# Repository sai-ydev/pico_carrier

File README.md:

# pico_carrier
Pico carrier board for the Blues Notecard

## TO DO ##
1. ~~Fix Eagle Lbr~~
2. ~~Fix PCB~~
3. Design StemmaQT Form factor

In the picture below, Raspberry Pi Pico interfaced to the [Blues Notecard](https://blues.io/)

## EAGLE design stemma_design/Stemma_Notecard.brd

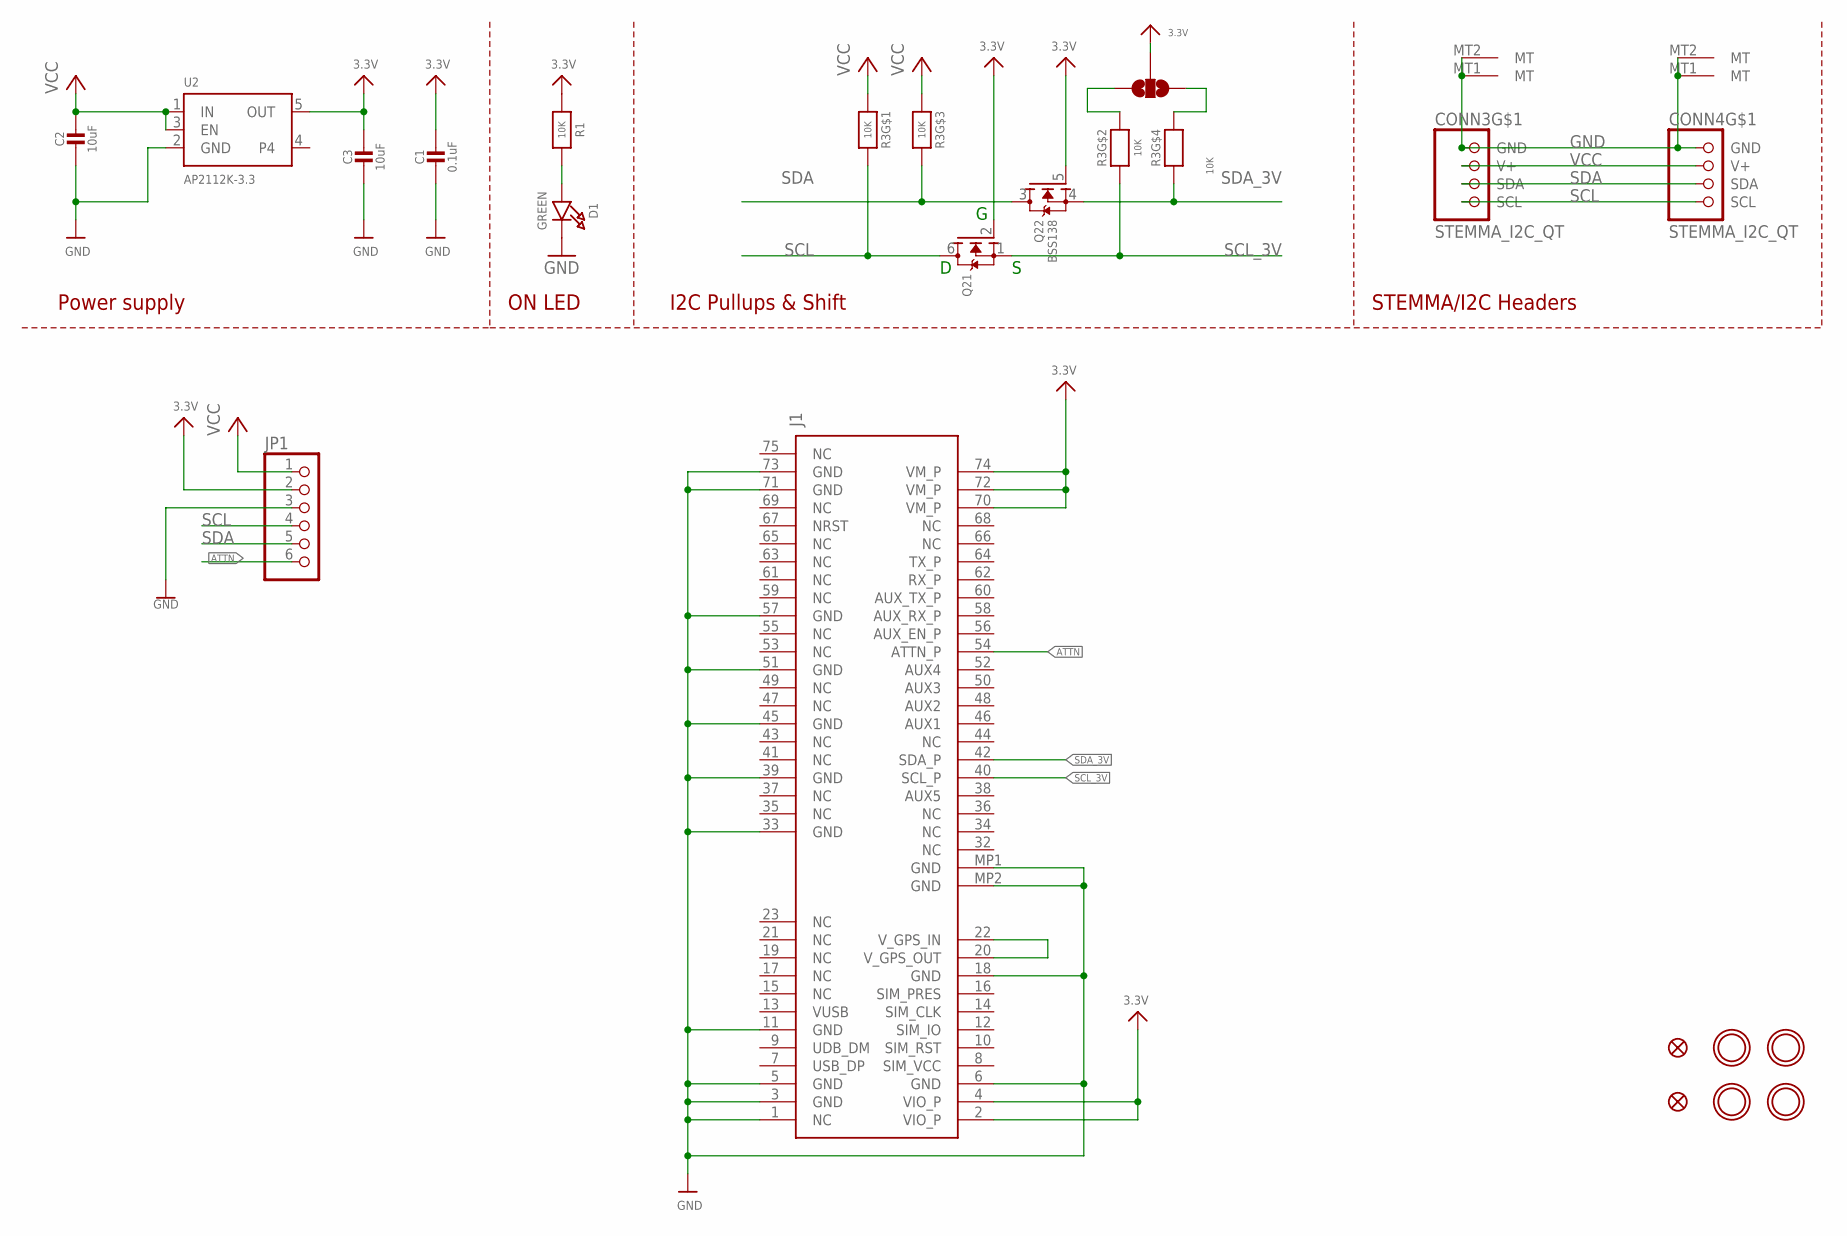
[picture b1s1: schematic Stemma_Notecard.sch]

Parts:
C1: 0.1uF; 0603-NO
C2, C3: 10uF; 0805-NO
CONN3, CONN4: STEMMA_I2C_QT; JST_SH4
D1: GREEN; CHIPLED_0603_NOOUTLINE
FID3, FID4: FIDUCIAL_1MM
J1: MDT420E01001NOTECARD; NOTECARD
JP1: HEADER-1X670MIL; 1X06_ROUND_70
JP2: JUMPER-SMT_3_NO_NO-SILK; SMT-JUMPER_3_NO_NO-SILK
Q2: BSS138; SOT363
R1: 10K; 0603-NO
R3: 10K; RESPACK_4X0603
U2: AP2112K-3.3; SOT23-5
U$1, U$17, U$19, U$21: MOUNTINGHOLE2.5; MOUNTINGHOLE_2.5_PLATED

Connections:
3.3V: C1.1, C3.1, J1.2 (VIO_P), J1.4 (VIO_P), J1.70 (VM_P), J1.72 (VM_P), J1.74 (VM_P), JP1.2, JP2.2, Q2.2 (G), Q2.5 (G), R1.1, U2.5 (OUT)
ATTN: J1.54 (ATTN_P), JP1.6
GND: C1.2, C2.2, C3.2, CONN3.1 (GND), CONN3.MT1 (MT), CONN3.MT2 (MT), CONN4.1 (GND), CONN4.MT1 (MT), CONN4.MT2 (MT), D1.C, J1.1 (NC), J1.3 (GND), J1.5 (GND), J1.6 (GND), J1.11 (GND), J1.18 (GND), J1.33 (GND), J1.39 (GND), J1.45 (GND), J1.51 (GND), J1.57 (GND), J1.71 (GND), J1.73 (GND), J1.MP1 (GND), J1.MP2 (GND), JP1.3, U2.2 (GND)
unnamed: D1.A, R1.2
unnamed: J1.20 (V_GPS_OUT), J1.22 (V_GPS_IN)
unnamed: JP2.3, R3.2 (1)
unnamed: JP2.1, R3.4 (1)
SCL: CONN3.4 (SCL), CONN4.4 (SCL), JP1.4, Q2.6 (D), R3.8 (2)
SCL_3V: J1.40 (SCL_P), Q2.1 (S), R3.7 (2)
SDA: CONN3.3 (SDA), CONN4.3 (SDA), JP1.5, Q2.3 (D), R3.6 (2)
SDA_3V: J1.42 (SDA_P), Q2.4 (S), R3.5 (2)
VCC: C2.1, CONN3.2 (V+), CONN4.2 (V+), JP1.1, R3.1, R3.3 (1), U2.1 (IN), U2.3 (EN)

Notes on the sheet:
I2C Pullups & Shift
STEMMA/I2C Headers
ON LED
Power supply

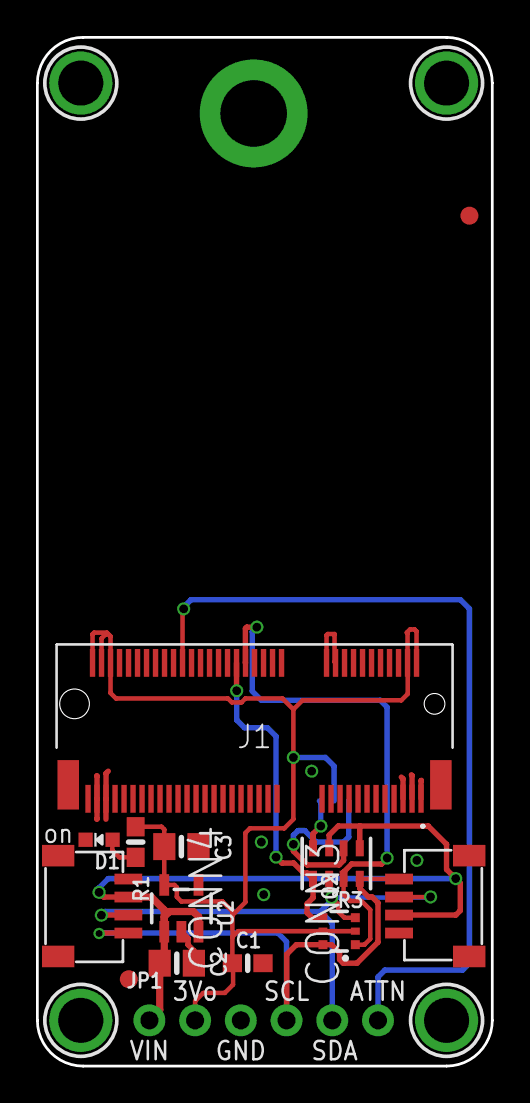
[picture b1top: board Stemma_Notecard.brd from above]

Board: 2 copper layers, 25.3 x 57.1 mm, 19 parts (1 on the bottom side), 12 nets.

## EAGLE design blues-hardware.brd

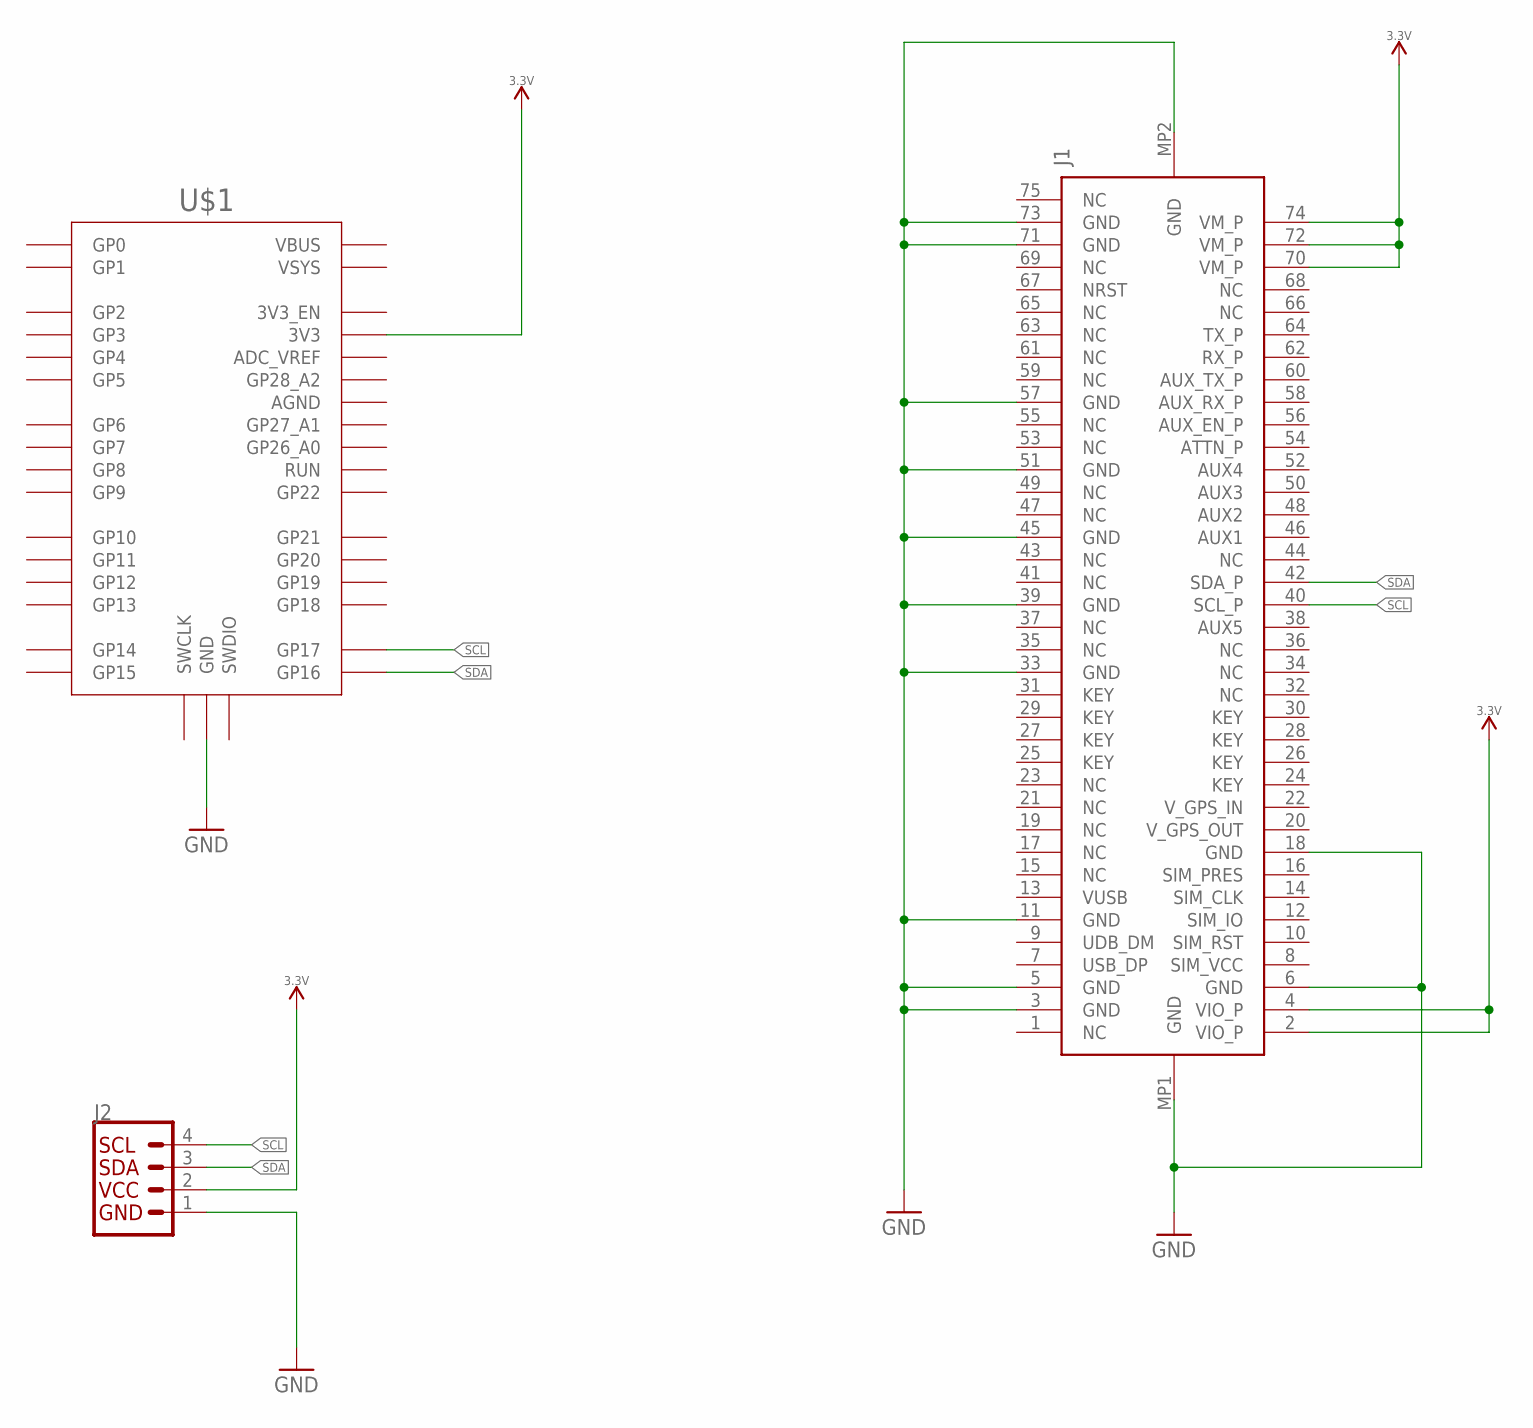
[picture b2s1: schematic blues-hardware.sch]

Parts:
J1: MDT420E01001NOTECARD; NOTECARD
J2: QWIIC_CONNECTORJS-1MM; 1X04_1MM_RA
U$1: RPI_PICO-TH; RPI_PICO_TH

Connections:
3.3V: J1.2 (VIO_P), J1.4 (VIO_P), J1.70 (VM_P), J1.72 (VM_P), J1.74 (VM_P), J2.2, U$1.3V3
GND: J1.3 (GND), J1.5 (GND), J1.6 (GND), J1.11 (GND), J1.18 (GND), J1.33 (GND), J1.39 (GND), J1.45 (GND), J1.51 (GND), J1.57 (GND), J1.71 (GND), J1.73 (GND), J1.MP1 (GND), J1.MP2 (GND), J2.1, U$1.GND@1 (GND), U$1.GND@2 (GND), U$1.GND@3 (GND), U$1.GND@4 (GND), U$1.GND@5 (GND), U$1.GND@6 (GND), U$1.GND@7 (GND), U$1.GND@8 (GND)
SCL: J1.40 (SCL_P), J2.4, U$1.GP17
SDA: J1.42 (SDA_P), J2.3, U$1.GP16

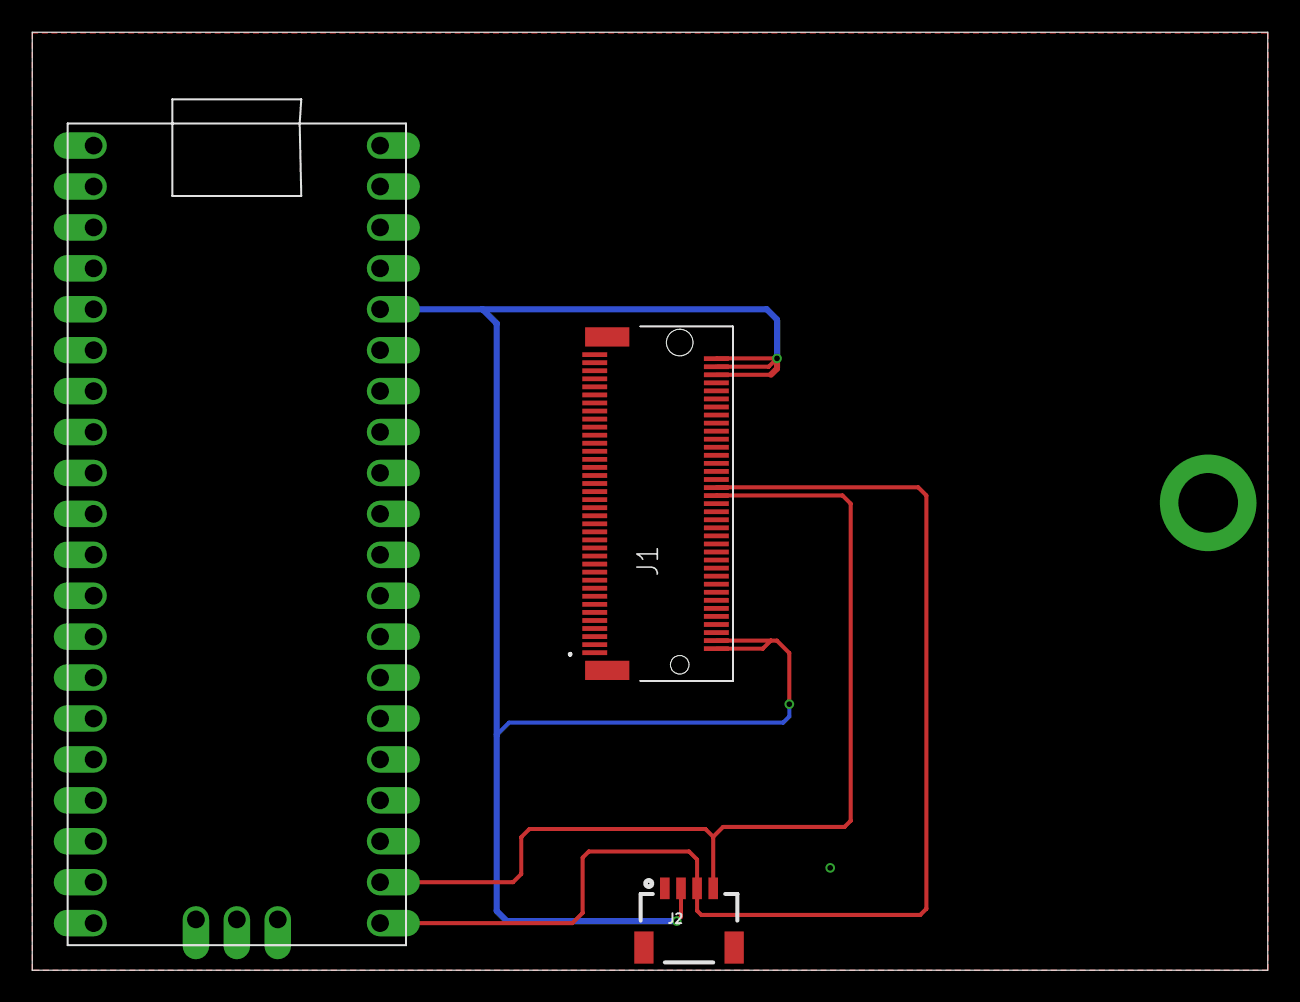
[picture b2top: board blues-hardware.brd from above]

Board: 2 copper layers, 76.7 x 58.2 mm, 3 parts (0 on the bottom side), 4 nets.

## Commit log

2021-04-01 Checking in files
2021-04-01 Changes to notecard library
2021-04-02 Check in
2021-04-03 stemma design upload

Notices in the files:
parts and their libraries:
SparkFun-Connectors: Licensing: Creative Commons ShareAlike 4.0 International - https://creativecommons.org/licenses/by-sa/4.0
microbuilder: This work is placed in the public domain, and may be freely used for commercial and non-commercial work with the following conditions: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
